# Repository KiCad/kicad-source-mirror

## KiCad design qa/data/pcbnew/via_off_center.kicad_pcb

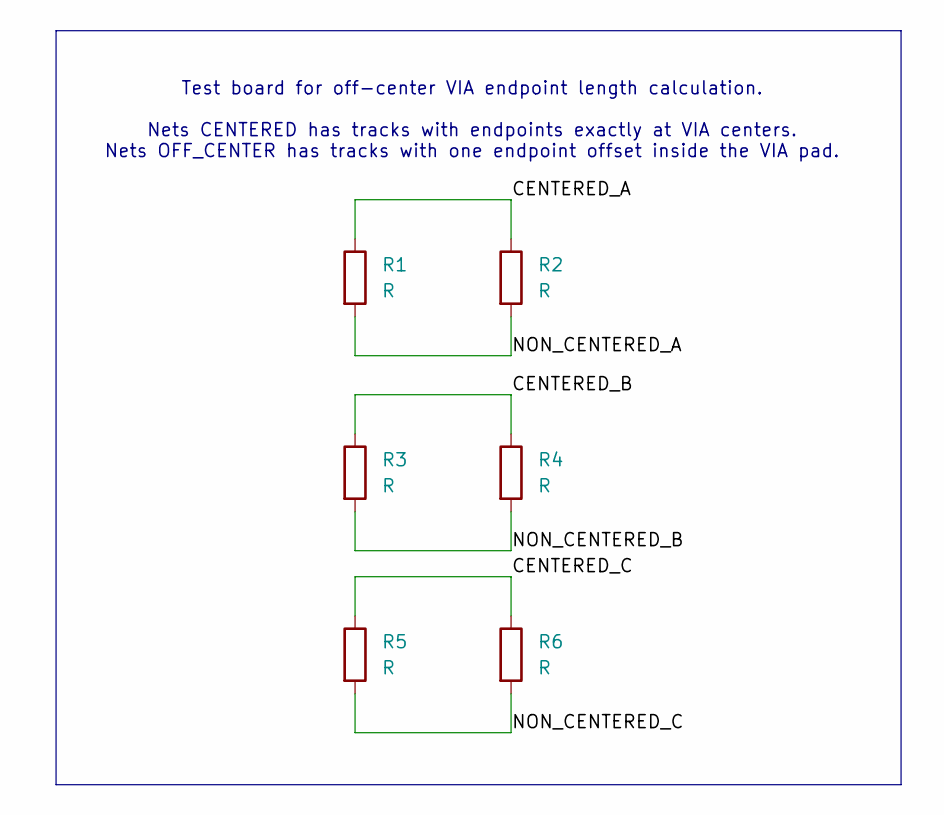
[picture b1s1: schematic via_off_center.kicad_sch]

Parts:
R1, R2, R3, R4, R5, R6: R; R_0805_2012Metric

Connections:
/CENTERED_A: R1.1, R2.1
/CENTERED_B: R3.1, R4.1
/CENTERED_C: R5.1, R6.1
/NON_CENTERED_A: R1.2, R2.2
/NON_CENTERED_B: R3.2, R4.2
/NON_CENTERED_C: R5.2, R6.2

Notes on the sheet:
Test board for off-center VIA endpoint length calculation. Nets CENTERED has tracks with endpoints exactly at VIA centers. Nets OFF_CENTER has tracks with one endpoint offset inside the VIA pad.

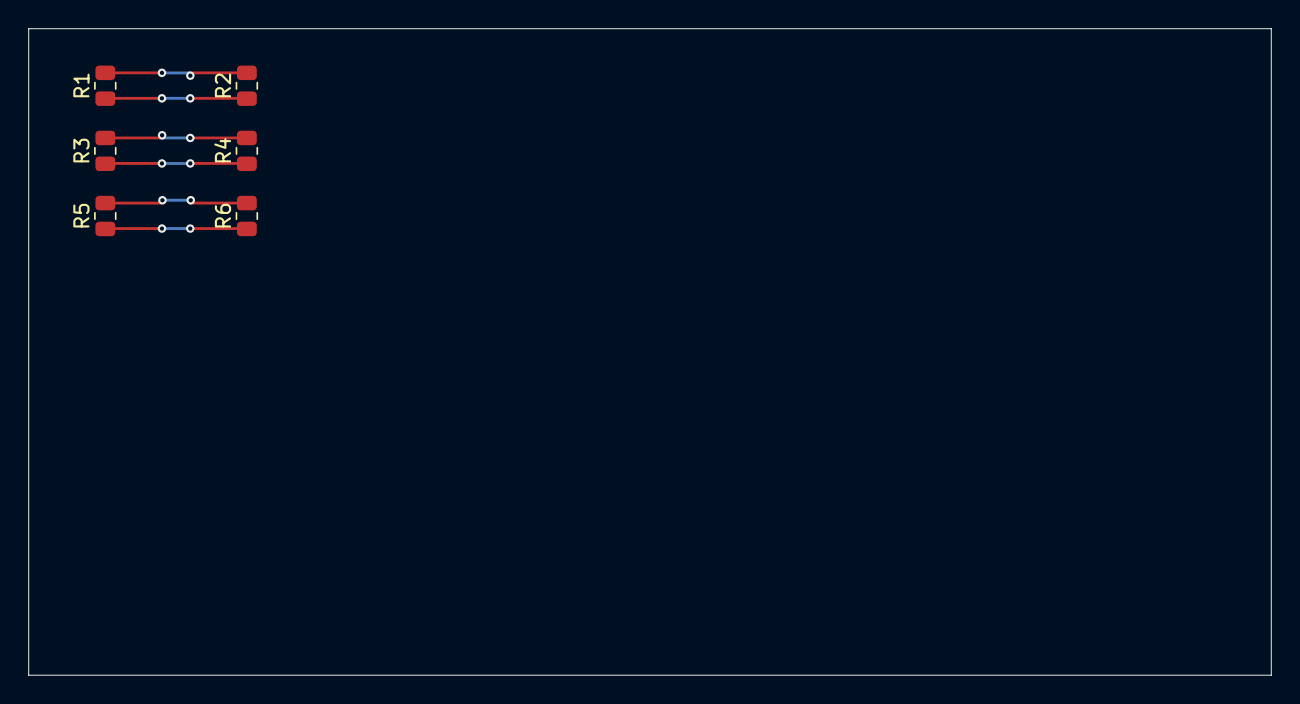
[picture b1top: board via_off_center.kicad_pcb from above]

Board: 4 copper layers, 87.8 x 45.7 mm, 6 parts (0 on the bottom side), 6 nets.
